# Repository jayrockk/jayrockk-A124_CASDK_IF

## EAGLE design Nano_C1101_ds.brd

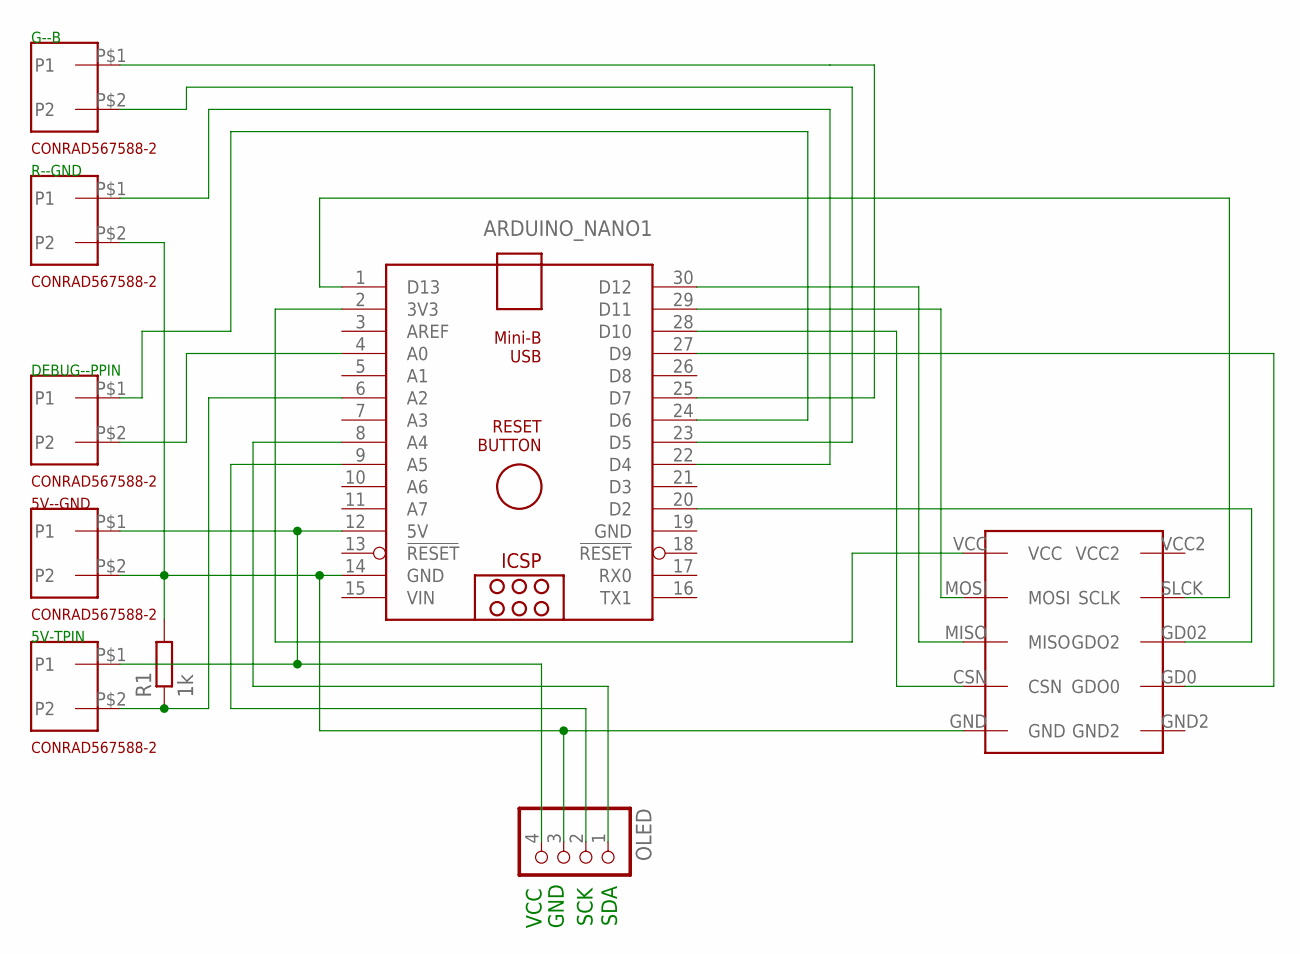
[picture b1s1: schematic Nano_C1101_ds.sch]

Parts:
5V--GND, 5V-TPIN: CONRAD567588-2; CONRAD567588
ARDUINO_NANO1: ARDUINO_NANO
DEBUG--PPIN: CONRAD567588-2; CONRAD567588
G--B: CONRAD567588-2; CONRAD567588
OLED: PINHD-1X4; 1X04
R1: 1k; 0204/7
R--GND: CONRAD567588-2; CONRAD567588
U$1: NEUFTECH_CC1101; NEUFTECH_CC1101_PACKAGE_BOTTOM_VIEW

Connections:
3V3: ARDUINO_NANO1.2 (3V3), U$1.VCC
5V: 5V--GND.P$1 (P1), 5V-TPIN.P$1 (P1), ARDUINO_NANO1.12 (5V), OLED.4
B-RGB: ARDUINO_NANO1.23 (D5), G--B.P$2 (P2)
CSN: ARDUINO_NANO1.28 (D10), U$1.CSN
DEBUG: ARDUINO_NANO1.24 (D6), DEBUG--PPIN.P$1 (P1)
G-RGB: ARDUINO_NANO1.25 (D7), G--B.P$1 (P1)
GDO0: ARDUINO_NANO1.27 (D9), U$1.GD0 (GDO0)
GDO2: ARDUINO_NANO1.20 (D2), U$1.GD02 (GDO2)
GND: 5V--GND.P$2 (P2), ARDUINO_NANO1.14 (GND), ARDUINO_NANO1.19 (GND), OLED.3, R1.2, R--GND.P$2 (P2), U$1.GND
MISO: ARDUINO_NANO1.30 (D12), U$1.MISO
MOSI: ARDUINO_NANO1.29 (D11), U$1.MOSI
PPIN: ARDUINO_NANO1.4 (A0), DEBUG--PPIN.P$2 (P2)
R-RGB: ARDUINO_NANO1.22 (D4), R--GND.P$1 (P1)
SCK: ARDUINO_NANO1.9 (A5), OLED.2
SCLK: ARDUINO_NANO1.1 (D13), U$1.SLCK (SCLK)
SDA: ARDUINO_NANO1.8 (A4), OLED.1
TPIN: 5V-TPIN.P$2 (P2), ARDUINO_NANO1.6 (A2), R1.1
VIN: ARDUINO_NANO1.15 (VIN)

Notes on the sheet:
VCC
GND
SCK
SDA

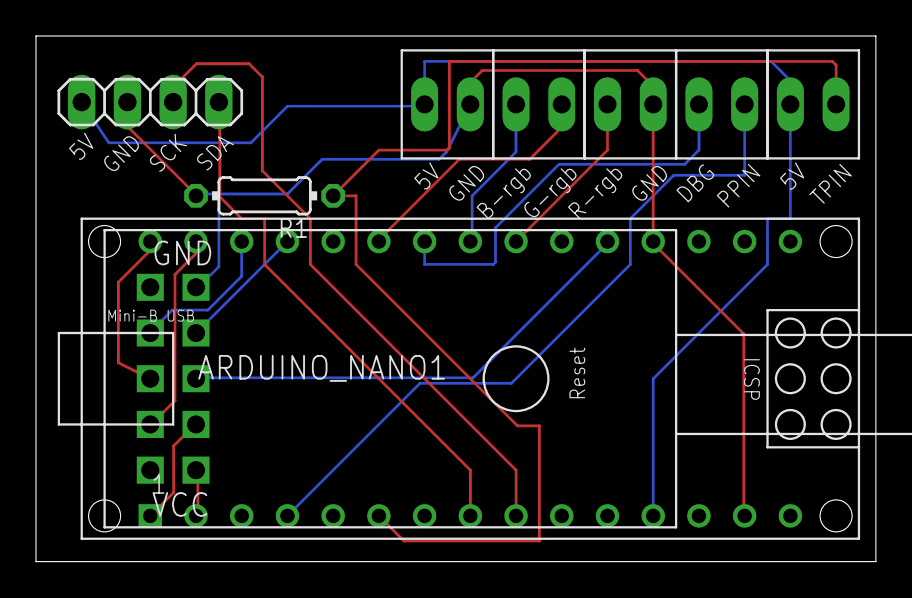
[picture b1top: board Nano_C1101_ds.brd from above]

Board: 2 copper layers, 46.7 x 29.2 mm, 9 parts (0 on the bottom side), 17 nets.

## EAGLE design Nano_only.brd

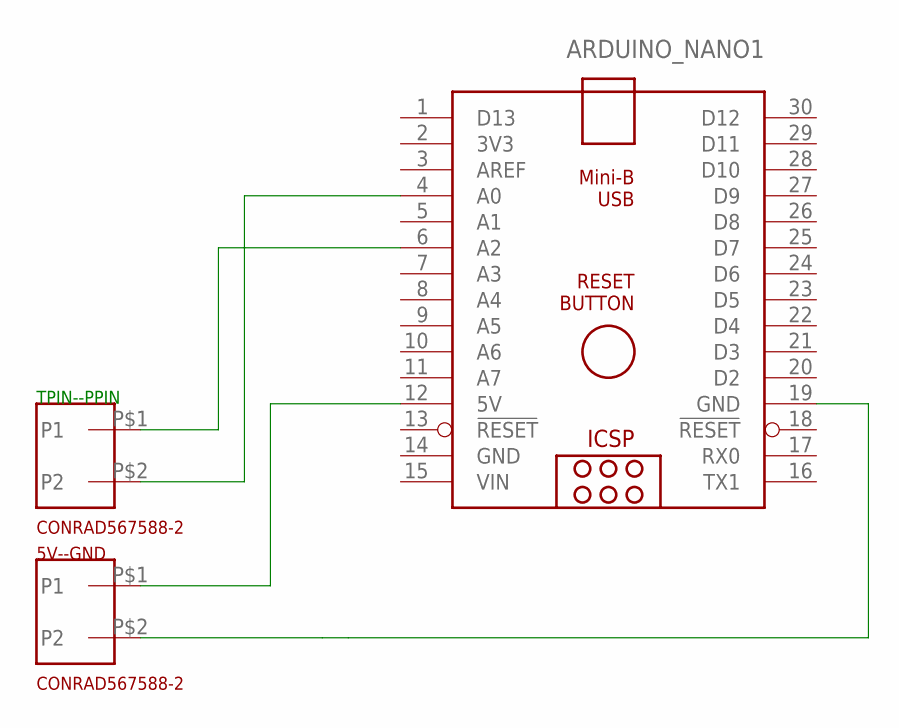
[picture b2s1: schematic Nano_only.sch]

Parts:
5V--GND: CONRAD567588-2; CONRAD567588
ARDUINO_NANO1: ARDUINO_NANO
TPIN--PPIN: CONRAD567588-2; CONRAD567588

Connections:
5V: 5V--GND.P$1 (P1), ARDUINO_NANO1.12 (5V)
GND: 5V--GND.P$2 (P2), ARDUINO_NANO1.14 (GND), ARDUINO_NANO1.19 (GND)
PPIN: ARDUINO_NANO1.4 (A0), TPIN--PPIN.P$2 (P2)
TPIN: ARDUINO_NANO1.6 (A2), TPIN--PPIN.P$1 (P1)
VIN: ARDUINO_NANO1.15 (VIN)

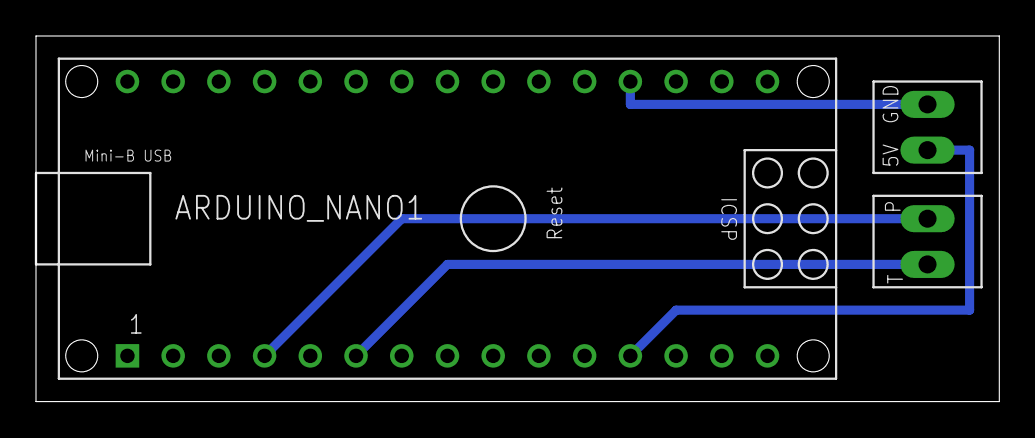
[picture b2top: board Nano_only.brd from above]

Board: 2 copper layers, 53.5 x 20.3 mm, 3 parts (0 on the bottom side), 4 nets.

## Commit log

2020-02-10 added pdf printout of Nano_only
2020-02-10 Added labels to Nano_only.brd
2020-02-10 Added some text on Nano_only.brd
2020-02-10 few typos, 3V3 -> 5V
2020-02-13 Semi-final version of Nano_C1101
2020-02-14 Added resistor and more pins for sensors
2020-02-14 Some more clearance in Nano_C1101.brd
2020-02-14 Added double sided variant Nano_C1101_ds.*
2020-02-16 Added text on PCB
